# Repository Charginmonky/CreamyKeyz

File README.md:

# CreamyKeyz
An ergonomic wireless keyboard with creamy switches for the ultimate creamy feel.

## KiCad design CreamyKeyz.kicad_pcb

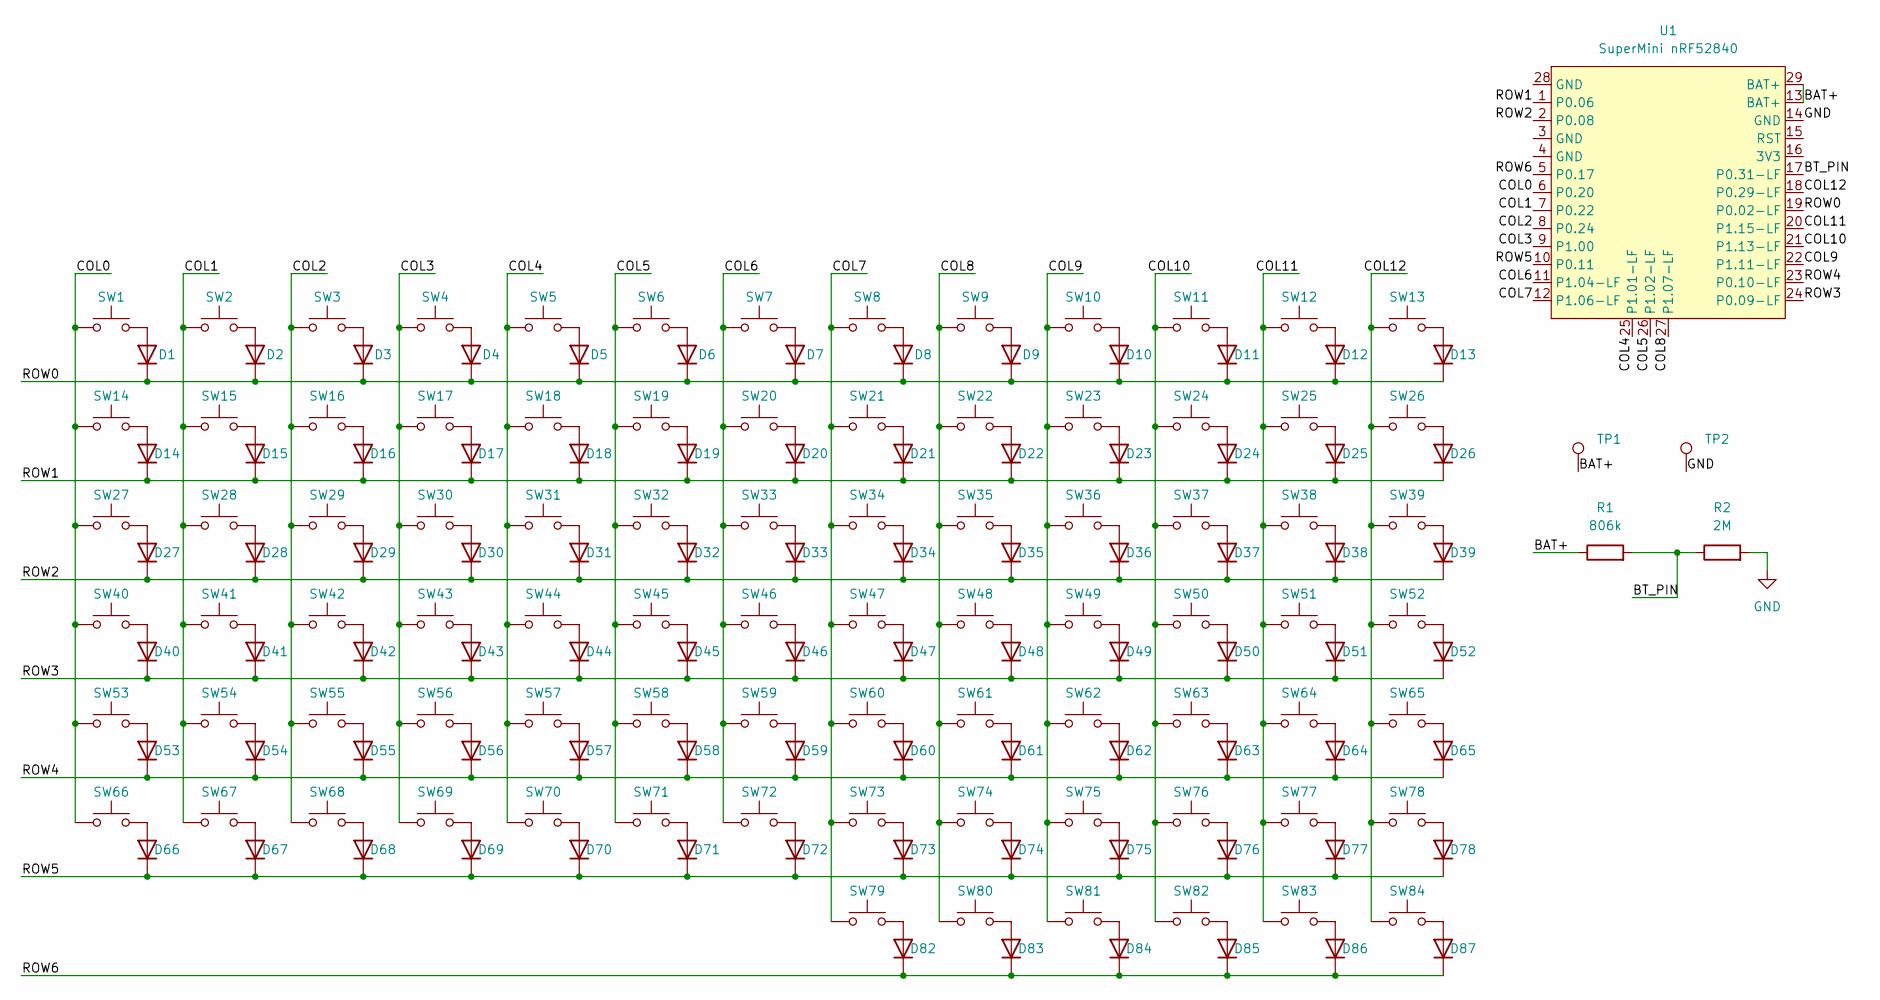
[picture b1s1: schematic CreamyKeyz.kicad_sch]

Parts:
D1, D2, D3, D4, D5, D6, D7, D8, D9, D10, D11, D12, D13, D14, D15, D16, D17, D18, D19, D20, D21, D22, D23, D24, D25, D26, D27, D28, D29, D30, D31, D32, D33, D34, D35, D36, D37, D38, D39, D40, D41, D42, D43, D44, D45, D46, D47, D48, D49, D50, D51, D52, D53, D54, D55, D56, D57, D58, D59, D60, D61, D62, D63, D64, D65, D66, D67, D68, D69, D70, D71, D72, D73, D74, D75, D76, D77, D78, D82, D83, D84, D85, D86, D87: D; D_DO-35_SOD27_P7.62mm_Horizontal
R1: 806k; R_0805_2012Metric
R2: 2M; R_0805_2012Metric
SW1, SW2, SW3, SW4, SW5, SW6, SW7, SW8, SW9, SW10, SW11, SW12, SW13, SW14, SW15, SW16, SW17, SW18, SW19, SW20, SW21, SW22, SW23, SW24, SW25, SW26, SW27, SW28, SW29, SW30, SW32, SW33, SW34, SW35, SW36, SW37, SW38, SW39, SW40, SW41, SW42, SW43, SW45, SW46, SW47, SW49, SW50, SW51, SW52, SW53, SW54, SW55, SW56, SW57, SW58, SW59, SW60, SW61, SW62, SW63, SW64, SW65, SW66, SW67, SW68, SW69, SW70, SW71, SW72, SW73, SW77, SW82, SW83, SW84: SW_Push; SW_MX_1u
SW31, SW44: SW_Push; SW_MX_1.5u
SW48: SW_Push; SW_MX_1.75u
SW74, SW75, SW76, SW78, SW79, SW80, SW81: SW_Push; SW_MX_1.25u
TP1, TP2: TestPoint; TestPoint_Pad_D1.5mm
U1: SuperMini nRF52840; SuperMini_nRF52840_AH_USBup

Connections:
/BAT+: R1.1, TP1.1, U1.13 (BAT+), U1.29 (BAT+)
/BT_PIN: R1.2, R2.1, U1.17 (P0.31-LF)
/COL0: SW1.1, SW14.1, SW27.1, SW40.1, SW53.1, SW66.1, U1.6 (P0.20)
/COL1: SW2.1, SW15.1, SW28.1, SW41.1, SW54.1, SW67.1, U1.7 (P0.22)
/COL2: SW3.1, SW16.1, SW29.1, SW42.1, SW55.1, SW68.1, U1.8 (P0.24)
/COL3: SW4.1, SW17.1, SW30.1, SW43.1, SW56.1, SW69.1, U1.9 (P1.00)
/COL4: SW5.1, SW18.1, SW31.1, SW44.1, SW57.1, SW70.1, U1.25 (P1.01-LF)
/COL5: SW6.1, SW19.1, SW32.1, SW45.1, SW58.1, SW71.1, U1.26 (P1.02-LF)
/COL6: SW7.1, SW20.1, SW33.1, SW46.1, SW59.1, SW72.1, U1.11 (P1.04-LF)
/COL7: SW8.1, SW21.1, SW34.1, SW47.1, SW60.1, SW73.1, SW79.1, U1.12 (P1.06-LF)
/COL8: SW9.1, SW22.1, SW35.1, SW48.1, SW61.1, SW74.1, SW80.1, U1.27 (P1.07-LF)
/COL9: SW10.1, SW23.1, SW36.1, SW49.1, SW62.1, SW75.1, SW81.1, U1.22 (P1.11-LF)
/COL10: SW11.1, SW24.1, SW37.1, SW50.1, SW63.1, SW76.1, SW82.1, U1.21 (P1.13-LF)
/COL11: SW12.1, SW25.1, SW38.1, SW51.1, SW64.1, SW77.1, SW83.1, U1.20 (P1.15-LF)
/COL12: SW13.1, SW26.1, SW39.1, SW52.1, SW65.1, SW78.1, SW84.1, U1.18 (P0.29-LF)
/ROW0: D1.1 (K), D2.1 (K), D3.1 (K), D4.1 (K), D5.1 (K), D6.1 (K), D7.1 (K), D8.1 (K), D9.1 (K), D10.1 (K), D11.1 (K), D12.1 (K), D13.1 (K), U1.19 (P0.02-LF)
/ROW1: D14.1 (K), D15.1 (K), D16.1 (K), D17.1 (K), D18.1 (K), D19.1 (K), D20.1 (K), D21.1 (K), D22.1 (K), D23.1 (K), D24.1 (K), D25.1 (K), D26.1 (K), U1.1 (P0.06)
/ROW2: D27.1 (K), D28.1 (K), D29.1 (K), D30.1 (K), D31.1 (K), D32.1 (K), D33.1 (K), D34.1 (K), D35.1 (K), D36.1 (K), D37.1 (K), D38.1 (K), D39.1 (K), U1.2 (P0.08)
/ROW3: D40.1 (K), D41.1 (K), D42.1 (K), D43.1 (K), D44.1 (K), D45.1 (K), D46.1 (K), D47.1 (K), D48.1 (K), D49.1 (K), D50.1 (K), D51.1 (K), D52.1 (K), U1.24 (P0.09-LF)
/ROW4: D53.1 (K), D54.1 (K), D55.1 (K), D56.1 (K), D57.1 (K), D58.1 (K), D59.1 (K), D60.1 (K), D61.1 (K), D62.1 (K), D63.1 (K), D64.1 (K), D65.1 (K), U1.23 (P0.10-LF)
/ROW5: D66.1 (K), D67.1 (K), D68.1 (K), D69.1 (K), D70.1 (K), D71.1 (K), D72.1 (K), D73.1 (K), D74.1 (K), D75.1 (K), D76.1 (K), D77.1 (K), D78.1 (K), U1.10 (P0.11)
/ROW6: D82.1 (K), D83.1 (K), D84.1 (K), D85.1 (K), D86.1 (K), D87.1 (K), U1.5 (P0.17)
GND: R2.2, TP2.1, U1.14 (GND)
unnamed: D1.2 (A), SW1.2
unnamed: D2.2 (A), SW2.2
unnamed: D3.2 (A), SW3.2
unnamed: D4.2 (A), SW4.2
unnamed: D5.2 (A), SW5.2
unnamed: D6.2 (A), SW6.2
unnamed: D7.2 (A), SW7.2
unnamed: D8.2 (A), SW8.2
unnamed: D9.2 (A), SW9.2
unnamed: D10.2 (A), SW10.2
unnamed: D11.2 (A), SW11.2
unnamed: D12.2 (A), SW12.2
unnamed: D13.2 (A), SW13.2
unnamed: D14.2 (A), SW14.2
unnamed: D15.2 (A), SW15.2
unnamed: D16.2 (A), SW16.2
unnamed: D17.2 (A), SW17.2
unnamed: D18.2 (A), SW18.2
unnamed: D19.2 (A), SW19.2
unnamed: D20.2 (A), SW20.2
unnamed: D21.2 (A), SW21.2
unnamed: D22.2 (A), SW22.2
unnamed: D23.2 (A), SW23.2
unnamed: D24.2 (A), SW24.2
unnamed: D25.2 (A), SW25.2
unnamed: D26.2 (A), SW26.2
unnamed: D27.2 (A), SW27.2
unnamed: D28.2 (A), SW28.2
unnamed: D29.2 (A), SW29.2
unnamed: D30.2 (A), SW30.2
unnamed: D31.2 (A), SW31.2
unnamed: D32.2 (A), SW32.2
unnamed: D33.2 (A), SW33.2
unnamed: D34.2 (A), SW34.2
unnamed: D35.2 (A), SW35.2
unnamed: D36.2 (A), SW36.2
unnamed: D37.2 (A), SW37.2
unnamed: D38.2 (A), SW38.2
unnamed: D39.2 (A), SW39.2
unnamed: D40.2 (A), SW40.2
unnamed: D41.2 (A), SW41.2
unnamed: D42.2 (A), SW42.2
unnamed: D43.2 (A), SW43.2
unnamed: D44.2 (A), SW44.2
unnamed: D45.2 (A), SW45.2
unnamed: D46.2 (A), SW46.2
unnamed: D47.2 (A), SW47.2
unnamed: D48.2 (A), SW48.2
unnamed: D49.2 (A), SW49.2
unnamed: D50.2 (A), SW50.2
unnamed: D51.2 (A), SW51.2
unnamed: D52.2 (A), SW52.2
unnamed: D53.2 (A), SW53.2
unnamed: D54.2 (A), SW54.2
unnamed: D55.2 (A), SW55.2
unnamed: D56.2 (A), SW56.2
unnamed: D57.2 (A), SW57.2
unnamed: D58.2 (A), SW58.2
unnamed: D59.2 (A), SW59.2
unnamed: D60.2 (A), SW60.2
unnamed: D61.2 (A), SW61.2
unnamed: D62.2 (A), SW62.2
unnamed: D63.2 (A), SW63.2
unnamed: D64.2 (A), SW64.2
unnamed: D65.2 (A), SW65.2
unnamed: D66.2 (A), SW66.2
unnamed: D67.2 (A), SW67.2
unnamed: D68.2 (A), SW68.2
unnamed: D69.2 (A), SW69.2
unnamed: D70.2 (A), SW70.2
unnamed: D71.2 (A), SW71.2
unnamed: D72.2 (A), SW72.2
unnamed: D73.2 (A), SW73.2
unnamed: D74.2 (A), SW74.2
unnamed: D75.2 (A), SW75.2
unnamed: D76.2 (A), SW76.2
unnamed: D77.2 (A), SW77.2
unnamed: D78.2 (A), SW78.2
unnamed: D82.2 (A), SW79.2
unnamed: D83.2 (A), SW80.2
unnamed: D84.2 (A), SW81.2
unnamed: D85.2 (A), SW82.2
unnamed: D86.2 (A), SW83.2
unnamed: D87.2 (A), SW84.2

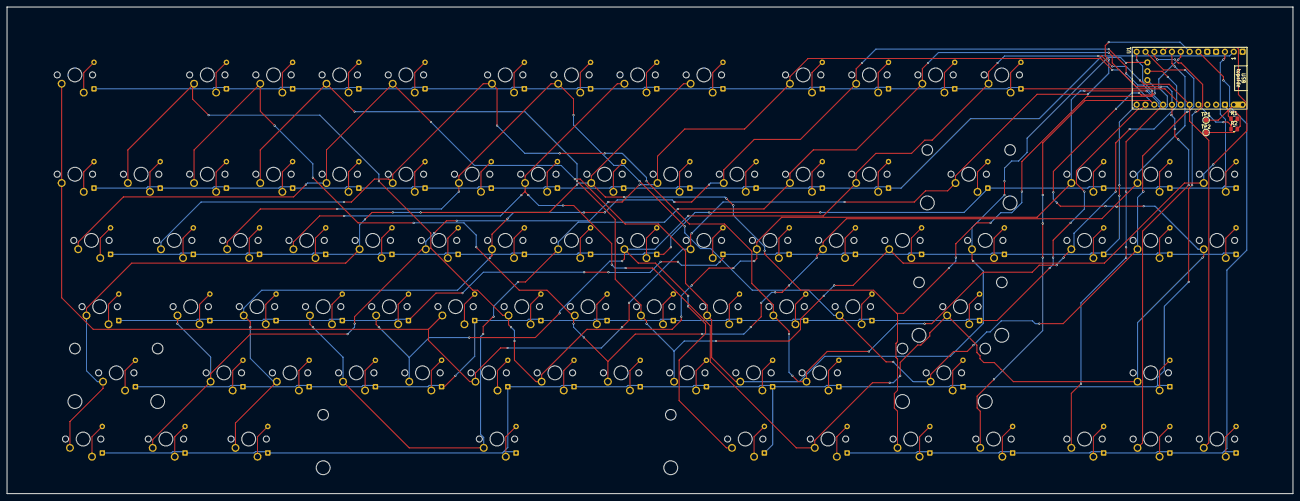
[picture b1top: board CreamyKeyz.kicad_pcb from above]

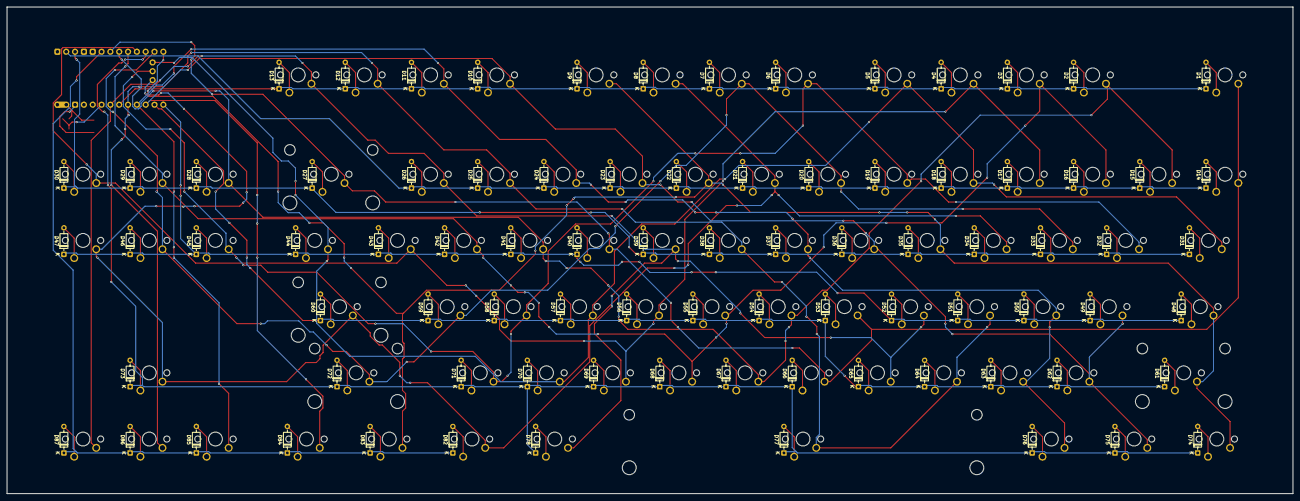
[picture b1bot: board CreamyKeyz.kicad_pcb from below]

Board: 2 copper layers, 370.0 x 140.0 mm, 173 parts (168 on the bottom side), 107 nets.
